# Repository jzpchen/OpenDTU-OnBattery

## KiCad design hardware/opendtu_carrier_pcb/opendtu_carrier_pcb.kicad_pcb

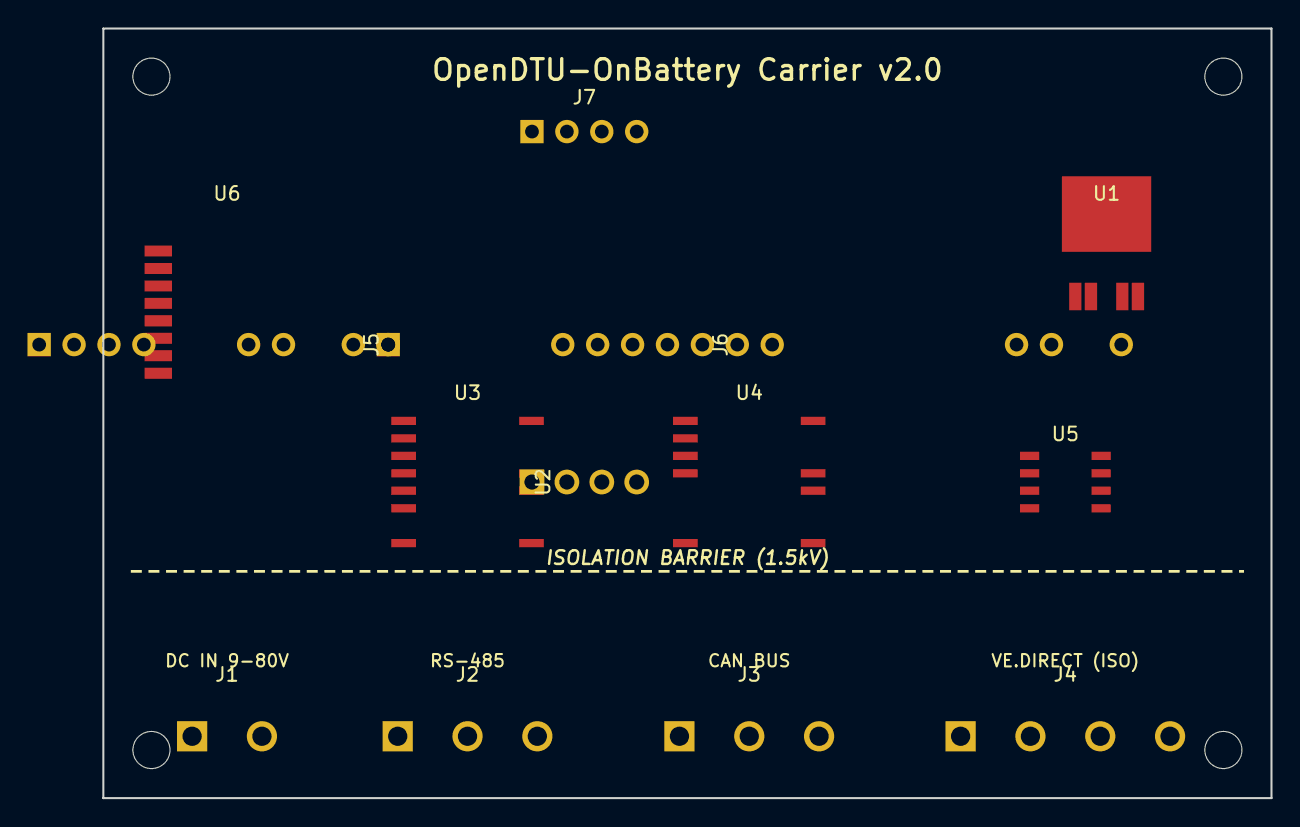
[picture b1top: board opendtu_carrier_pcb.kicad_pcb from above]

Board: 2 copper layers, 85.0 x 56.0 mm, 13 parts (0 on the bottom side), 28 nets, no tracks yet.

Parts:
J1: DC_IN_9-80V; TerminalBlock_Phoenix_MKDS-1,5-2-5.08_1x02_P5.08mm_Horizont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
J2: RS485_ISO; TerminalBlock_Phoenix_MKDS-1,5-3-5.08_1x03_P5.08mm_Horizont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
J3: CAN_ISO; TerminalBlock_Phoenix_MKDS-1,5-3-5.08_1x03_P5.08mm_Horizont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
J4: VEDIRECT_ISO; TerminalBlock_Phoenix_MKDS-1,5-4-5.08_1x04_P5.08mm_Horizont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
J5, J6: PinSocket_1x22_P2.54mm_Vertical
J7: OLED_2.4_I2C; PinSocket_1x04_P2.54mm_Vertical
U1: XL7015E1; TO-252-5_TabPin3
U2: B0505S-1WR3; Converter_DCDC_Mornsun_B0505S-1WR3_THT
U3: CA-IS3082WX; SOIC-16W_7.5x10.3mm_P1.27mm
U4: CA-IS3050G; SOIC-16W_7.5x10.3mm_P1.27mm
U5: ADuM1201ARZ; SOIC-8_3.9x4.9mm_P1.27mm
U6: CMT2300A_RF; HopeRF_RFM300W_SMD

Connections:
+3V3: J5.1, J7.2, U6.2
+5V: J5.22, U2.2, U3.1, U4.1, U5.1
+5V_ISO: U2.4, U3.16, U4.16
+5V_VE: J4.1, U5.8
CAN_H: J3.1, U4.13
CAN_L: J3.2, U4.12
CAN_RX: J6.20, U4.4
CAN_TX: J6.19, U4.3
CMT_CSB: J5.18, U6.5
CMT_FCSB: J5.19, U6.6
CMT_GPIO2: J5.20, U6.7
CMT_GPIO3: J5.21, U6.8
CMT_SCLK: J5.16, U6.4
CMT_SDIO: J5.17, U6.3
GND: J1.2, J6.1, J6.22, J7.1, U1.3, U1.5, U2.1, U3.2, U3.8, U4.2, U4.8, U5.4, U6.1
GND_ISO: J2.3, J3.3, U2.3, U3.9, U4.9
GND_VE: J4.4, U5.5
I2C_SCL: J5.3, J7.3
I2C_SDA: J5.4, J7.4
RS485_A: J2.1, U3.13
RS485_B: J2.2, U3.12
RS485_RX: J5.7, U3.3
RS485_TX: J5.8, U3.6
VE_RX_ESP: J5.10, U5.3
VE_RX_ISO: J4.2, U5.6
VE_TX_ESP: J5.11, U5.2
VE_TX_ISO: J4.3, U5.7
VIN: J1.1, U1.1

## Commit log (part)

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2026-06-02 Zendure: Bugfix: Accept non-static message ids (#2575)
    Seems that recent firmware versions (at least Hyper2000) increment the message id. This commit removes the check for static message id, so frames are accepted.
    This should fixe the issue mentioned in #2556
2026-06-13 Bugfix: Zendure: Increase allowed length of appkey to 16 characters (#2593)
2026-06-16 Feature: add SmartSolar 250/60 rev3 and 250/70 rev3 to list of known VE.Direct devices (#2604)
2026-06-18 build(deps): bump actions/checkout from 6 to 7 (#2606)
    Bumps [actions/checkout](https://github.com/actions/checkout) from 6 to 7.
    - [Release notes](https://github.com/actions/checkout/releases)
    - [Changelog](https://github.com/actions/checkout/blob/main/CHANGELOG.md)
    - [Commits](https://github.com/actions/checkout/compare/v6...v7)
    ---
    updated-dependencies:
2026-06-23 build(deps): bump mikepenz/release-changelog-builder-action (#2609)
    Bumps [mikepenz/release-changelog-builder-action](https://github.com/mikepenz/release-changelog-builder-action) from 6.2.2 to 6.2.3.
    - [Release notes](https://github.com/mikepenz/release-changelog-builder-action/releases)
    - [Commits](https://github.com/mikepenz/release-changelog-builder-action/compare/v6.2.2...v6.2.3)
    ---
    updated-dependencies:
    - dependency-name: mikepenz/release-changelog-builder-action
2026-06-24 build(deps): bump actions/cache from 5 to 6 (#2615)
    Bumps [actions/cache](https://github.com/actions/cache) from 5 to 6.
    - [Release notes](https://github.com/actions/cache/releases)
    - [Changelog](https://github.com/actions/cache/blob/main/RELEASES.md)
    - [Commits](https://github.com/actions/cache/compare/v5...v6)
    ---
    updated-dependencies:
